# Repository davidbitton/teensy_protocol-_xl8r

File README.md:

# teensy_protocol_xl8r

This is a rework of the Teensy 3.6 board with JST GH connectors for four (4) of the onboard UARTs. SPI0 is available on a header.

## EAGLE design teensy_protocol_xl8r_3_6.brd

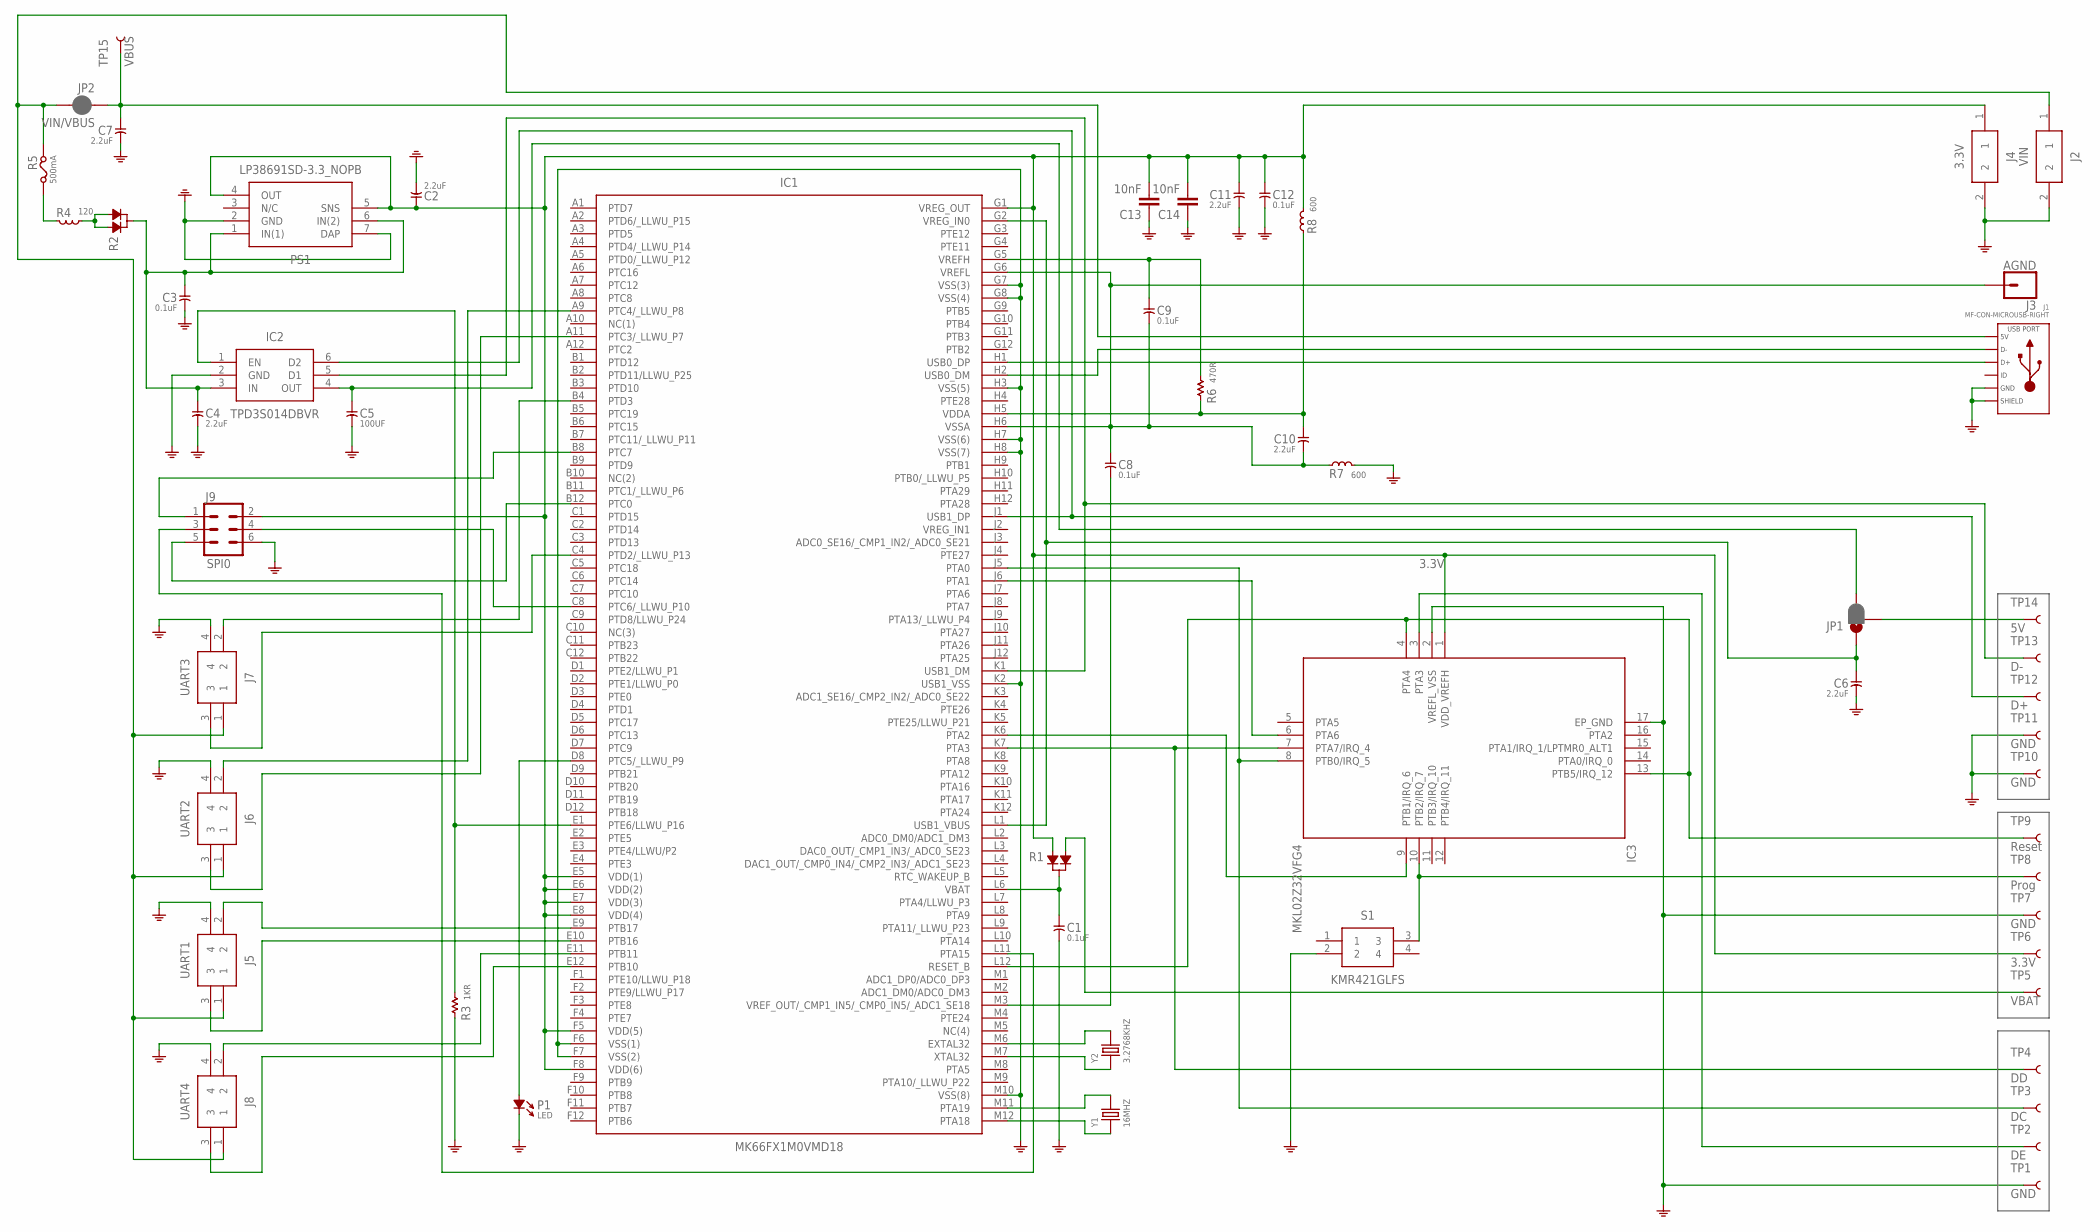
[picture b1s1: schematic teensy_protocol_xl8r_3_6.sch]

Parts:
C1, C3, C8, C9, C12: 0.1uF; C0603
C2, C4, C6, C7, C10, C11: 2.2uF; C0805
C5: 100UF; C1206
C13, C14: 10nF; 0603
IC1: MK66FX1M0VMD18; BGA144C100P12X12_1300X1300X170
IC2: TPD3S014DBVR; SOT95P280X145-6N
IC3: MKL02Z32VFG4; QFN50P300X300X65-17N
J1: MF-CON-MICROUSB-RIGHT; MICROUSB-RIGHT
J2: VIN; SM02B-GHS-TB
J3: AGND; 1X01
J4: 3.3V; SM02B-GHS-TB
J5: UART1; SM04B-GHS-TB
J6: UART2; SM04B-GHS-TB
J7: UART3; SM04B-GHS-TB
J8: UART4; SM04B-GHS-TB
J9: SPI0; 2X3
JP1: JUMPER-SMT_3_1-NC_PASTE_SILK; SMT-JUMPER_3_1-NC_PASTE_SILK
JP2: VIN/VBUS; SMT-JUMPER_2_NC_PASTE_SILK
P1: LED; LED-0805
PS1: LP38691SD-3.3_NOPB; SON95P300X300X80-7N
R1, R2: DIODE_DUAL; SOT-23
R3: 1KR; R0603
R4: 120; L0603
R5: 500mA; F0805
R6: 470R; R0603
R7, R8: 600; L0603
S1: KMR421GLFS; KMR_2
TP1, TP7, TP10, TP11: GND; PAD.03X.03
TP2: DE; PAD.03X.03
TP3: DC; PAD.03X.03
TP4: DD; PAD.03X.03
TP5: VBAT; PAD.03X.03
TP6: 3.3V; PAD.03X.03
TP8: Prog; PAD.03X.03
TP9: Reset; PAD.03X.03
TP12: D+; PAD.03X.03
TP13: D-; PAD.03X.03
TP14: 5V; PAD.03X.03
TP15: VBUS; PAD.03X.03
Y1: 16MHZ; X2-SMD-5.0X3.2X1.3MM
Y2: 3.2768KHZ; X2-SMD-L2.0X1.2X0.55MM

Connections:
3.3V: C2.1, C11.1, C12.1, C13.2, C14.2, IC1.E5 (VDD(1)), IC1.E6 (VDD(2)), IC1.E7 (VDD(3)), IC1.E8 (VDD(4)), IC1.F5 (VDD(5)), IC1.F8 (VDD(6)), IC1.G1 (VREG_OUT), IC3.1 (VDD_VREFH), J4.1, J9.2, PS1.4 (OUT), PS1.5 (SNS), R1.2, R8.2, TP6.P$1
CS0: IC1.B12 (PTC0), J9.5
GND: C1.2, C2.2, C3.2, C4.2, C5.2, C6.2, C7.2, C11.2, C12.2, C13.1, C14.1, IC1.F6 (VSS(1)), IC1.F7 (VSS(2)), IC1.G7 (VSS(3)), IC1.G8 (VSS(4)), IC1.H3 (VSS(5)), IC1.H7 (VSS(6)), IC1.H8 (VSS(7)), IC1.K2 (USB1_VSS), IC1.M10 (VSS(8)), IC2.2 (GND), IC3.2 (VREFL_VSS), IC3.17 (EP_GND), J1.5 (GND), J1.S1 (SLD), J1.S2 (SLD), J1.S3 (SLD), J1.S4 (SLD), J1.S5 (SLD), J1.S6 (SLD), J2.2, J4.2, J5.4, J6.4, J7.4, J8.4, J9.6, P1.-, PS1.2 (GND), PS1.7 (DAP), R3.1, R7.2, S1.2, TP1.P$1, TP7.P$1, TP10.P$1, TP11.P$1
MISO0: IC1.B8 (PTC7), J9.1
MOSI0: IC1.C8 (PTC6/_LLWU_P10), J9.4
unnamed: IC1.K7 (PTA3), IC3.7 (PTA7/IRQ_4), TP4.P$1
unnamed: IC1.J5 (PTA0), IC3.8 (PTB0/IRQ_5), TP3.P$1
unnamed: IC1.K6 (PTA2), IC3.9 (PTB1/IRQ_6)
unnamed: IC1.J6 (PTA1), IC3.6 (PTA6)
unnamed: IC1.L12 (RESET_B), IC3.4 (PTA4), IC3.13 (PTB5/IRQ_12), TP9.P$1
unnamed: IC3.10 (PTB2/IRQ_7), S1.3, TP8.P$1
unnamed: IC3.3 (PTA3), TP2.P$1
unnamed: C1.1, IC1.L6 (VBAT), R1.3
unnamed: IC1.E1 (PTE6/LLWU_P16), IC2.1 (EN), R3.2
unnamed: C3.1, C4.1, IC2.3 (IN), PS1.1 (IN(1)), PS1.6 (IN(2)), R2.3
unnamed: C5.1, IC2.4 (OUT), JP1.3
unnamed: C6.1, IC1.G2 (VREG_IN0), IC1.L1 (USB1_VBUS), JP1.1
unnamed: IC1.K1 (USB1_DM), IC2.5 (D1), TP13.P$1
unnamed: IC1.J1 (USB1_DP), IC2.6 (D2), TP12.P$1
unnamed: IC1.M6 (EXTAL32), Y2.2
unnamed: IC1.M7 (XTAL32), Y2.1
unnamed: JP1.2, TP14.P$1
unnamed: R2.1, R2.2, R4.2
unnamed: R4.1, R5.2
unnamed: IC1.M11 (PTA19), Y1.2
unnamed: IC1.M12 (PTA18), Y1.1
unnamed: C8.1, C9.2, C10.2, IC1.G6 (VREFL), IC1.H6 (VSSA), J3.1, R7.1
unnamed: C8.2, IC1.M3 (VREF_OUT/_CMP1_IN5/_CMP0_IN5/_ADC1_SE18)
unnamed: C9.1, IC1.G5 (VREFH), R6.2
unnamed: C10.1, IC1.H5 (VDDA), R6.1, R8.1
unnamed: IC1.D8 (PTC5/_LLWU_P9), P1.+
RX1: IC1.E9 (PTB17), J5.2
RX2: IC1.A11 (PTC3/_LLWU_P7), J6.3
RX3: IC1.C4 (PTD2/_LLWU_P13), J7.3
RX4: IC1.E12 (PTB10), J8.3
SCK0: IC1.L11 (PTA15), J9.3
TX1: IC1.E10 (PTB16), J5.3
TX2: IC1.A9 (PTC4/_LLWU_P8), J6.2
TX3: IC1.B4 (PTD3), J7.2
TX4: IC1.E11 (PTB11), J8.2
USB0_DM: IC1.H2 (USB0_DM), J1.2 (D-)
USB0_DP: IC1.H1 (USB0_DP), J1.3 (D+)
VBAT: R1.1, TP5.P$1
VBUS: C7.1, J1.1 (5V), JP2.1, TP15.P$1
VIN: J2.1, J5.1, J6.1, J7.1, J8.1, JP2.2, R5.1

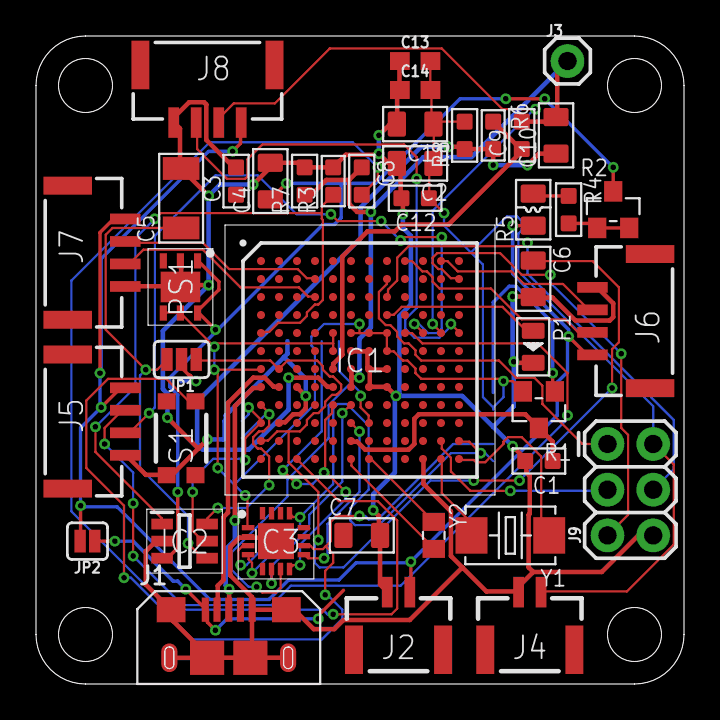
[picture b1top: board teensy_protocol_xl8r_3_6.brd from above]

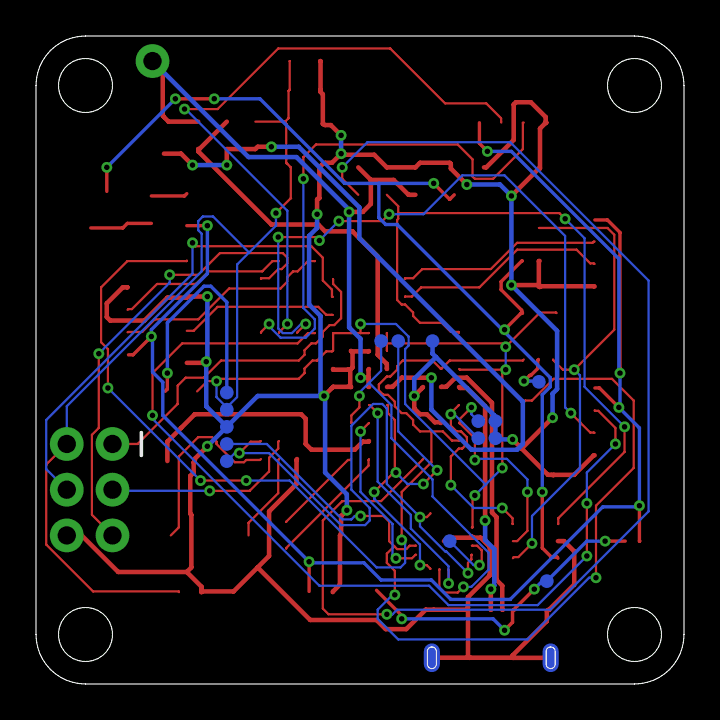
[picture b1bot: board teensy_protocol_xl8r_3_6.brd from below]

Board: 2 copper layers, 36.0 x 36.0 mm, 56 parts (15 on the bottom side), 45 nets.

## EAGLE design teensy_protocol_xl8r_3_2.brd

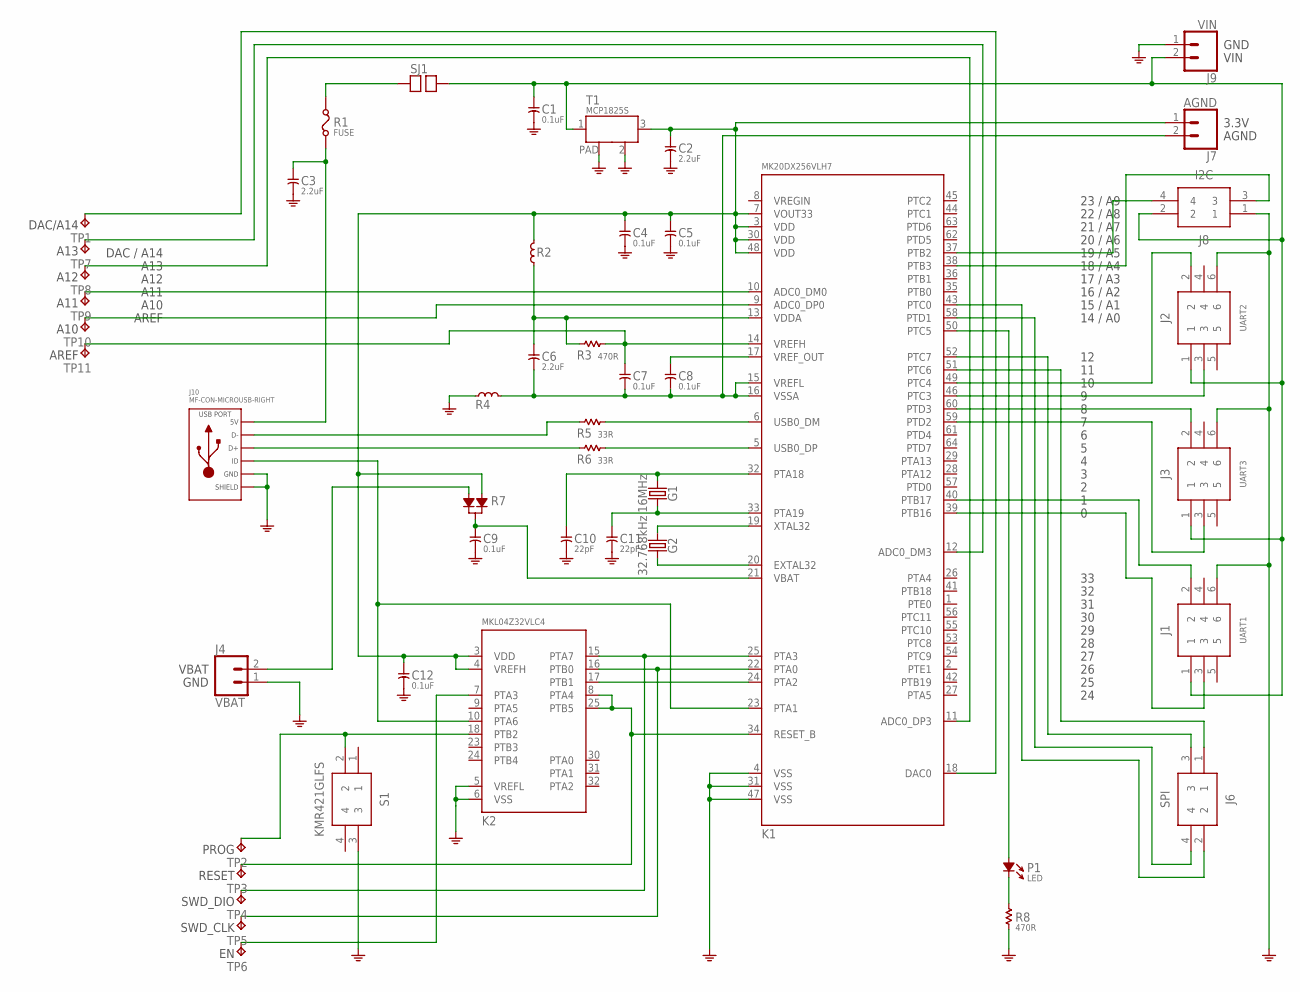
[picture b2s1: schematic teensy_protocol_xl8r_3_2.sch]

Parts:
C1, C4, C5, C7, C8, C9, C12: 0.1uF; C0603
C2, C3, C6: 2.2uF; C0805
C10, C11: 22pF; C0603
G1: 16MHz; CRYSTAL-SMD-5X3.2-4PAD
G2: 32.768kHz; CRYSTAL-SMD-3.2X1.5MM
J1: UART1; BM06B-GHS-TBT
J2: UART2; BM06B-GHS-TBT
J3: UART3; BM06B-GHS-TBT
J4: VBAT; 1X02
J6: SPI; BM04B-GHS-TBT
J7: AGND; 1X02
J8: I2C; BM04B-GHS-TBT
J9: VIN; 1X02
J10: MF-CON-MICROUSB-RIGHT; MICROUSB-RIGHT
K1: MK20DX256VLH7; LQFP64-05
K2: MKL04Z32VLC4; LQFP32-08
P1: LED; LED-0805
R1: FUSE; F0805
R2, R4: FERRITE; L0603
R3, R8: 470R; R0603
R5, R6: 33R; R0603
R7: DIODE_DUAL; SOT-23
S1: KMR421GLFS; KMR_2
SJ1: VUSB; SOLDERJUMPER
T1: MCP1825S; SOT-223
TP1, TP2, TP3, TP4, TP5, TP6, TP7, TP8, TP9, TP10, TP11: TPTP06R; TP06R

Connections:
CS: J6.2, K1.43 (PTC0)
DIN: J6.3, K1.52 (PTC7)
DOUT: J6.1, K1.51 (PTC6)
GND: C1.2, C2.2, C3.2, C4.2, C5.2, C9.2, C10.2, C11.2, C12.2, J1.6, J2.6, J3.6, J4.1, J8.1, J9.1, J10.5 (GND), J10.S1 (SLD), J10.S2 (SLD), J10.S3 (SLD), J10.S4 (SLD), J10.S5 (SLD), J10.S6 (SLD), K1.4 (VSS), K1.31 (VSS), K1.47 (VSS), K2.5 (VREFL), K2.6 (VSS), R4.1, R8.1, S1.3, T1.2 (GND), T1.PAD
unnamed: K2.7 (PTA3), TP6.TP
unnamed: K1.22 (PTA0), K2.16 (PTB0), TP5.TP
unnamed: K1.24 (PTA2), K2.17 (PTB1)
unnamed: C10.1, G1.1, K1.32 (PTA18)
unnamed: C11.1, G1.3 (2), K1.33 (PTA19)
unnamed: G2.P$1 (1), K1.19 (XTAL32)
unnamed: G2.P$2 (2), K1.20 (EXTAL32)
unnamed: K2.18 (PTB2), S1.2, TP2.TP
unnamed: K1.5 (USB0_DP), R6.2
unnamed: C8.1, K1.17 (VREF_OUT)
unnamed: K1.34 (RESET_B), K2.8 (PTA4), K2.25 (PTB5), TP3.TP
unnamed: C7.1, K1.14 (VREFH), R3.2, TP11.TP
unnamed: K1.6 (USB0_DM), R5.2
unnamed: C6.1, K1.13 (VDDA), R2.1, R3.1
unnamed: J8.4, K1.37 (PTB2)
unnamed: J8.3, K1.38 (PTB3)
unnamed: K1.50 (PTC5), P1.+
unnamed: J2.2, K1.49 (PTC4)
unnamed: J2.3, K1.46 (PTC3)
unnamed: J3.2, K1.60 (PTD3)
unnamed: J3.3, K1.59 (PTD2)
unnamed: J1.2, K1.40 (PTB17)
unnamed: J1.3, K1.39 (PTB16)
unnamed: K1.12 (ADC0_DM3), TP7.TP
unnamed: P1.-, R8.2
unnamed: C6.2, C7.2, C8.2, J7.2, K1.15 (VREFL), K1.16 (VSSA), R4.2
unnamed: K1.18 (DAC0), TP1.TP
unnamed: K1.11 (ADC0_DP3), TP8.TP
unnamed: J4.2, R7.2
unnamed: K1.10 (ADC0_DM0), TP9.TP
unnamed: K1.9 (ADC0_DP0), TP10.TP
unnamed: R1.2, SJ1.1
unnamed: C9.1, K1.21 (VBAT), R7.3
unnamed: C2.1, C4.1, C5.1, C12.1, J7.1, K1.3 (VDD), K1.7 (VOUT33), K1.30 (VDD), K1.48 (VDD), K2.3 (VDD), K2.4 (VREFH), R2.2, R7.1, T1.3 (OUT)
unnamed: K1.25 (PTA3), K2.15 (PTA7), TP4.TP
SCK: J6.4, K1.58 (PTD1)
USB0_DM: J10.2 (D-), R5.1
USB0_DP: J10.3 (D+), R6.1
USB0_ID: J10.4 (ID), K1.23 (PTA1), K2.10 (PTA6)
VBUS: C3.1, J10.1 (5V), R1.1
VIN: C1.1, J1.1, J2.1, J3.1, J8.2, J9.2, SJ1.2, T1.1 (IN)

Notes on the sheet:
VIN
AGND
3.3V
23 / A9
22 / A8
21 / A7
20 / A6
19 / A5
18 / A4
17 / A3
16 / A2
15 / A1
14 / A0
A13
A12
DAC / A14
GND
VBAT
A11
A10
AREF

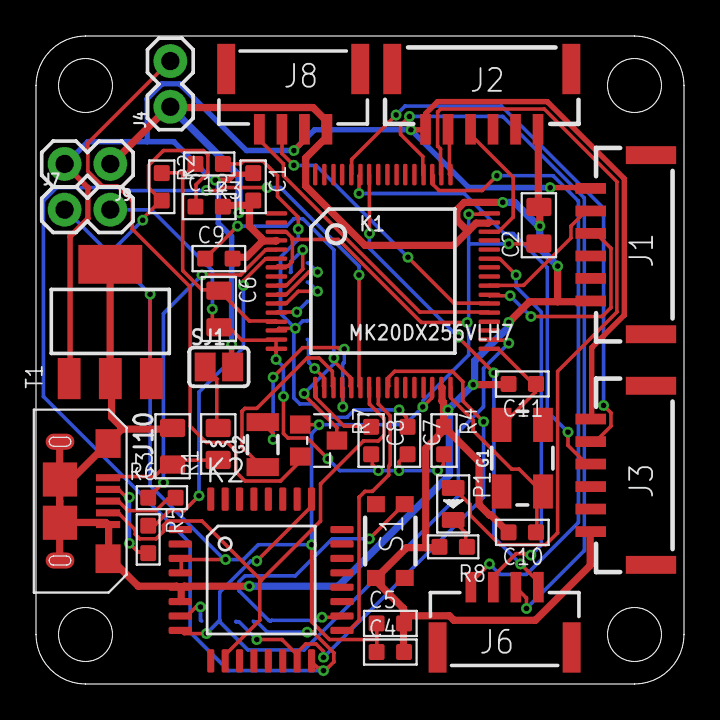
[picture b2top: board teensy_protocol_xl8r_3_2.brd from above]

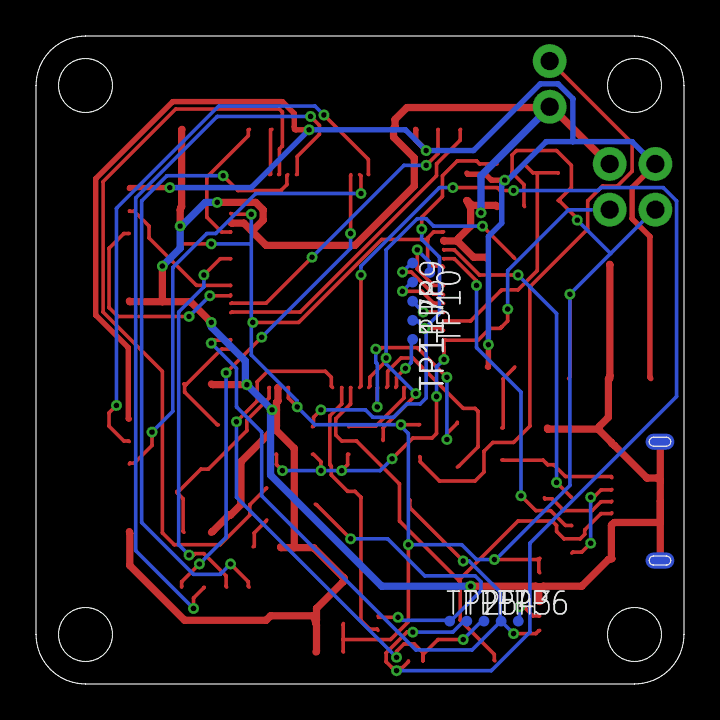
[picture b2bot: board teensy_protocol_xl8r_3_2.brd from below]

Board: 2 copper layers, 36.0 x 36.0 mm, 48 parts (11 on the bottom side), 45 nets.

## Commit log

2018-01-19 removed old cam files
2018-01-19 gitignore

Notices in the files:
parts and their libraries:
SparkFun-Connectors: Licensing: Creative Commons ShareAlike 4.0 International - https://creativecommons.org/licenses/by-sa/4.0
